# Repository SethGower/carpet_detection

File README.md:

# Carpet Detection PCB for CMPE-460 NXP Cup Autonomous Vehicle race

This is the carpet detection circuit I designed for the NXP/Freescale Cup race.
The purpose of it is to add hardware carpet detection to the car, by using the
OPB745 opto-isolator sensor to detect if the car is on the track. If the sensor
is above the carpet, the output of the amplifier will be high, and the
micro-controller will be able to read this on a GPIO pin. If it is on the
carpet, the output of the amplifier will be low, providing a voltage drop across
the LED, lighting up the LED (red). 

Part was designed using KiCAD.

## Hardware
### Schematic

### PCB
Front | Back
:-----:|:-----:
 | 

3D View

Idea inspired by a suggestion from Louis Beato

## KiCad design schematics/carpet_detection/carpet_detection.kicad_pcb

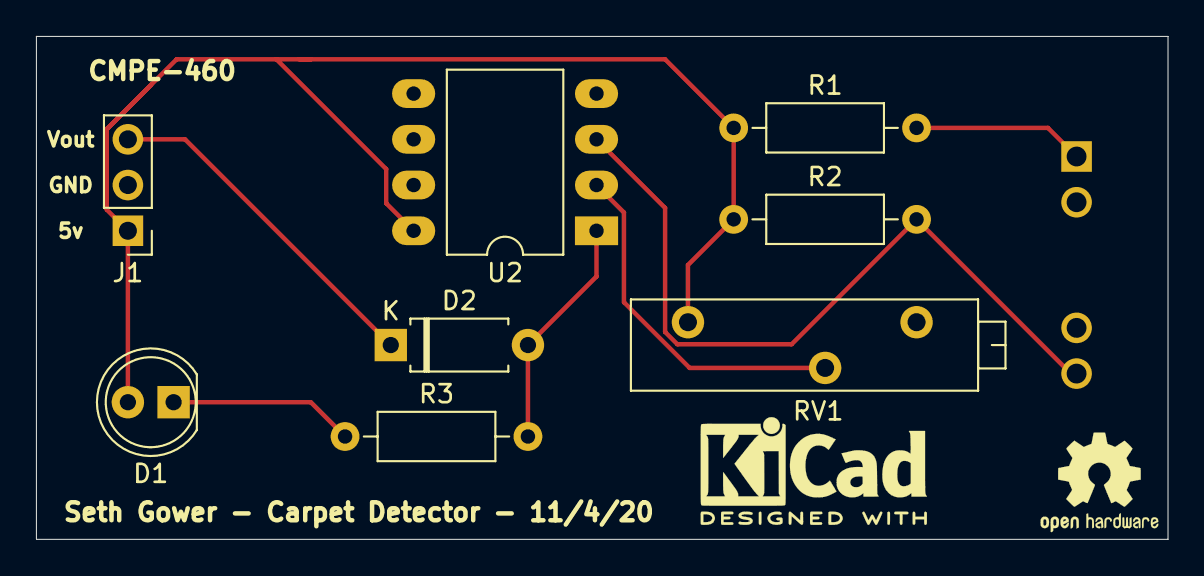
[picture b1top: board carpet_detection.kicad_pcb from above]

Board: 2 copper layers, 62.9 x 27.9 mm, 9 parts (1 on the bottom side), 8 nets.

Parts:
D1: Red; LED_D5.0mm
D2: D; D_A-405_P7.62mm_Horizontal
J1: Conn_01x03; PinHeader_1x03_P2.54mm_Vertical
R1, R2: R_US; R_Axial_DIN0207_L6.3mm_D2.5mm_P10.16mm_Horizontal
R3: 1k; R_Axial_DIN0207_L6.3mm_D2.5mm_P10.16mm_Horizontal
RV1: R_POT_US; Potentiometer_Bourns_3006P_Horizontal
U1: OPB745; TT_Electronics-OPB745-0
U2: TLC277; DIP-8_W10.16mm_LongPads

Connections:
+5V: D1.2, J1.1, R1.1, R2.1, RV1.1, U2.8
/Vin: R2.2, U1.4, U2.3
/Vo: D2.2, R3.2, U2.1
/Vref: RV1.2, U2.2
GND: J1.2, RV1.3, U1.2, U1.3, U2.4
unnamed: D1.1, R3.1
unnamed: R1.2, U1.1
Vout: D2.1, J1.3

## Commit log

2020-11-14 Adds Schematic for carpet detection
2020-11-14 updates schemaitic to use trimpot for Vref
2020-11-14 Adds LEDS to the carpet detector
2020-11-14 Removes Green LED, moves OPB745 to bottom, everything else to top
2020-11-14 Final revision of the PCB. Ordered on OSH Park
2020-11-14 Actually finishes the PCB.
2020-11-14 Adds readme
2020-11-14 Adds images to readme
2020-11-14 fixes table on readme
